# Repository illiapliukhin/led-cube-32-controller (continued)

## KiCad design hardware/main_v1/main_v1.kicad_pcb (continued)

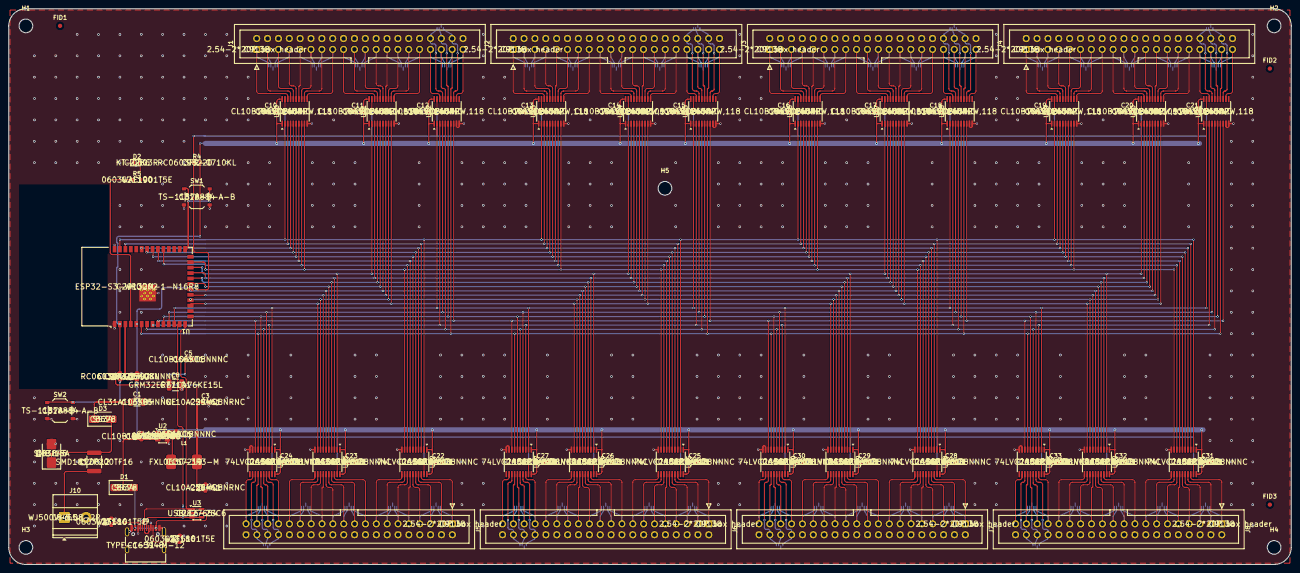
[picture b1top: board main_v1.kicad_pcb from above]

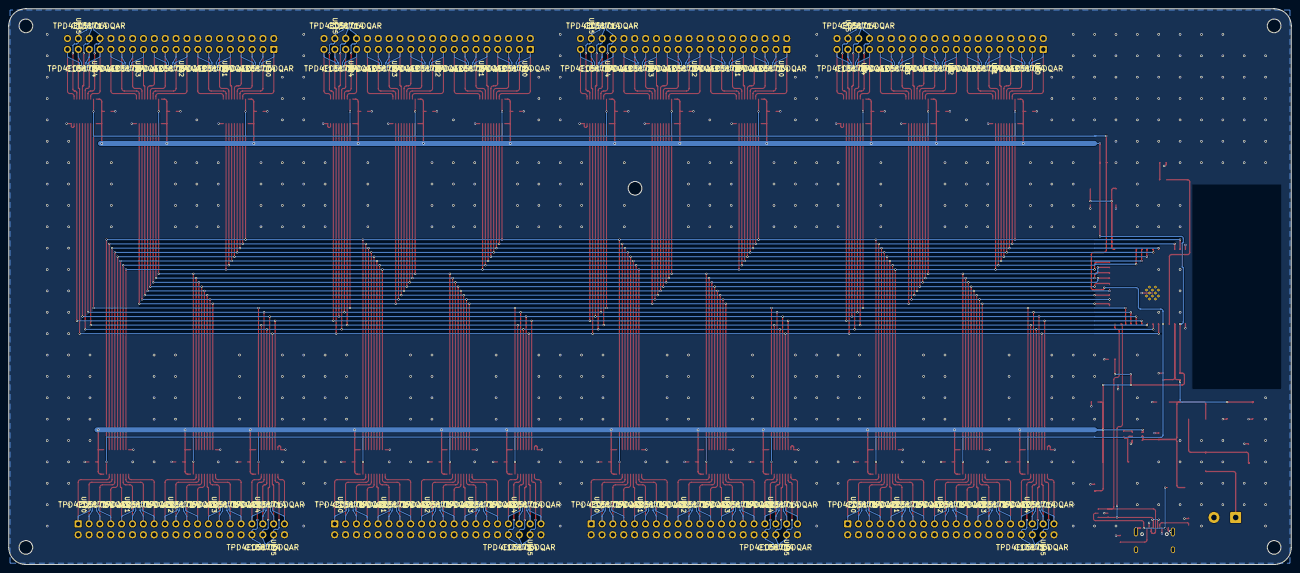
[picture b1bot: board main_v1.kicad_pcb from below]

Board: 2 copper layers, 300.0 x 130.0 mm, 138 parts (48 on the bottom side), 224 nets.

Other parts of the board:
FID1, FID2, FID3: FID; Fiducial_1mm_Mask2mm
H1, H2, H3, H4, H5: M3; MountingHole_3.2mm_M3

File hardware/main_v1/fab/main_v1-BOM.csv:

Comment,Designator,Footprint,LCSC Part #,MPN,Qty
10uF50V,C1,C_1206_3216Metric,C13585,CL31A106KBHNNNE,1
100nF,"C10,C11,C12,C13,C14,C15,C16,C17,C18,C19,C2,C20,C21,C22,C23,C24,C25,C26,C27,C28,C29,C30,C31,C32,C33,C5,C7",C_0603_1608Metric,C66501,CL10B104KO8NNNC,27
22uF,"C3,C4",C_0603_1608Metric,C59461,CL10A226MQ8NRNC,2
1uF,C6,C_0603_1608Metric,C1592,CL10A105KO8NNNC,1
47uF,C8,C_1210_3225Metric,C77101,GRM32ER61C476KE15L,1
SS34,D1,D_SMA,C8678,SS34,1
STATUS,D2,LED_0603_1608Metric,C2286,KT-0603R,1
SS34 (rev.pol.),D3,D_SMA,C8678,SS34,1
SMBJ15A,D4,D_SMB,C83846,SMBJ15A,1
PTC 2A/16V,F1,Fuse_1812_4532Metric,C20812,SMD1812P200TF16,1
PORT0,J1,IDC-Header_2x20_P2.54mm_Vertical,C9138,2.54-2*20P box header,1
12V_IN,J10,"TerminalBlock_Phoenix_MKDS-1,5-2-5.08_1x02_P5.08mm_Horizontal",C8465,WJ500V-5.08-2P,1
PORT1,J2,IDC-Header_2x20_P2.54mm_Vertical,C9138,2.54-2*20P box header,1
PORT2,J3,IDC-Header_2x20_P2.54mm_Vertical,C9138,2.54-2*20P box header,1
PORT3,J4,IDC-Header_2x20_P2.54mm_Vertical,C9138,2.54-2*20P box header,1
PORT4,J5,IDC-Header_2x20_P2.54mm_Vertical,C9138,2.54-2*20P box header,1
PORT5,J6,IDC-Header_2x20_P2.54mm_Vertical,C9138,2.54-2*20P box header,1
PORT6,J7,IDC-Header_2x20_P2.54mm_Vertical,C9138,2.54-2*20P box header,1
PORT7,J8,IDC-Header_2x20_P2.54mm_Vertical,C9138,2.54-2*20P box header,1
USB-C,J9,USB_C_Receptacle_HRO_TYPE-C-31-M-12,C165948,TYPE-C-31-M-12,1
3.3uH,L1,L_Cjiang_FXL0630,C167219,FXL0630-3R3-M,1
10k,"R1,R4",R_0603_1608Metric,C98220,RC0603FR-0710KL,2
5.1k,"R2,R3",R_0603_1608Metric,C23186,0603WAF5101T5E,2
1k,R5,R_0603_1608Metric,C21190,0603WAF1001T5E,1
BOOT,SW1,SW_Push_1P1T_XKB_TS-1187A,C318884,TS-1187A-B-A-B,1
RESET,SW2,SW_Push_1P1T_XKB_TS-1187A,C318884,TS-1187A-B-A-B,1
ESP32-S3-WROOM-1-N16R8,U1,ESP32-S3-WROOM-1,C2913202,ESP32-S3-WROOM-1-N16R8,1
74LVC245APW,"U10,U11,U12,U13,U14,U15,U16,U17,U18,U19,U20,U21,U22,U23,U24,U25,U26,U27,U28,U29,U30,U31,U32,U33",TSSOP-20_4.4x6.5mm_P0.65mm,C6082,"74LVC245APW,118",24
AP63203WU-7,U2,TSOT-23-6,C780769,AP63203WU-7,1
USBLC6-2SC6,U3,SOT-23-6,C2827654,USBLC6-2SC6,1
TPD4E05U06DQAR,"UE0,UE1,UE10,UE11,UE12,UE13,UE14,UE15,UE2,UE20,UE21,UE22,UE23,UE24,UE25,UE3,UE30,UE31,UE32,UE33,UE34,UE35,UE4,UE40,UE41,UE42,UE43,UE44,UE45,UE5,UE50,UE51,UE52,UE53,UE54,UE55,UE60,UE61,UE62,UE63,UE64,UE65,UE70,UE71,UE72,UE73,UE74,UE75",USON-10_2.5x1.0mm_P0.5mm,C138714,TPD4E05U06DQAR,48

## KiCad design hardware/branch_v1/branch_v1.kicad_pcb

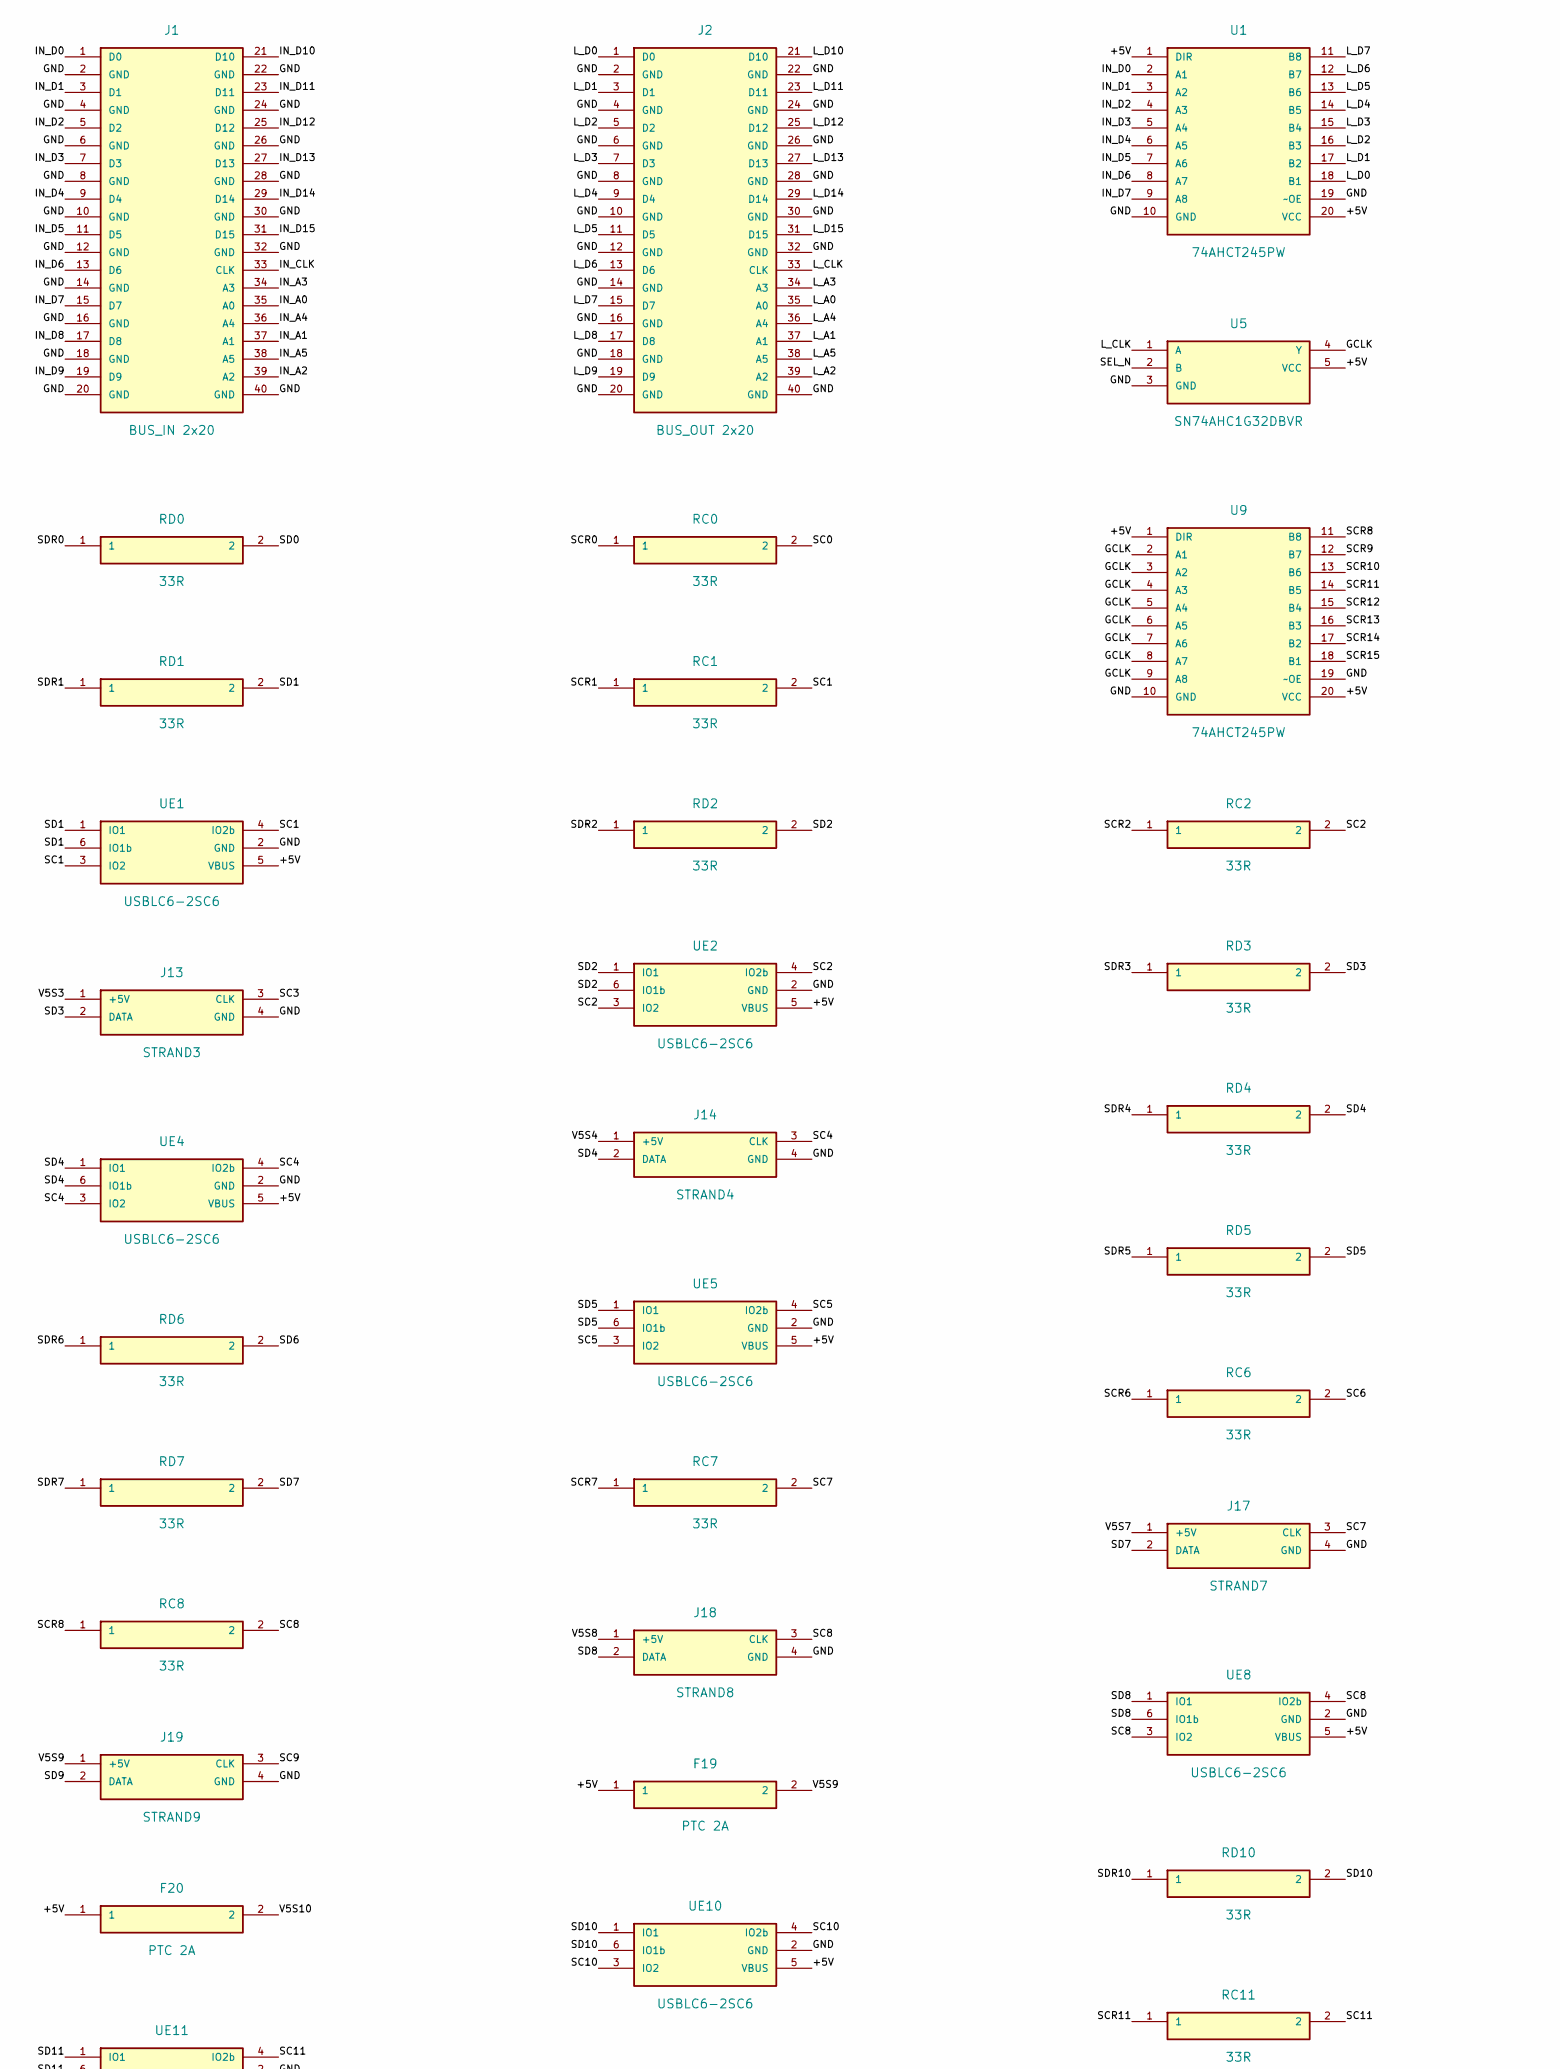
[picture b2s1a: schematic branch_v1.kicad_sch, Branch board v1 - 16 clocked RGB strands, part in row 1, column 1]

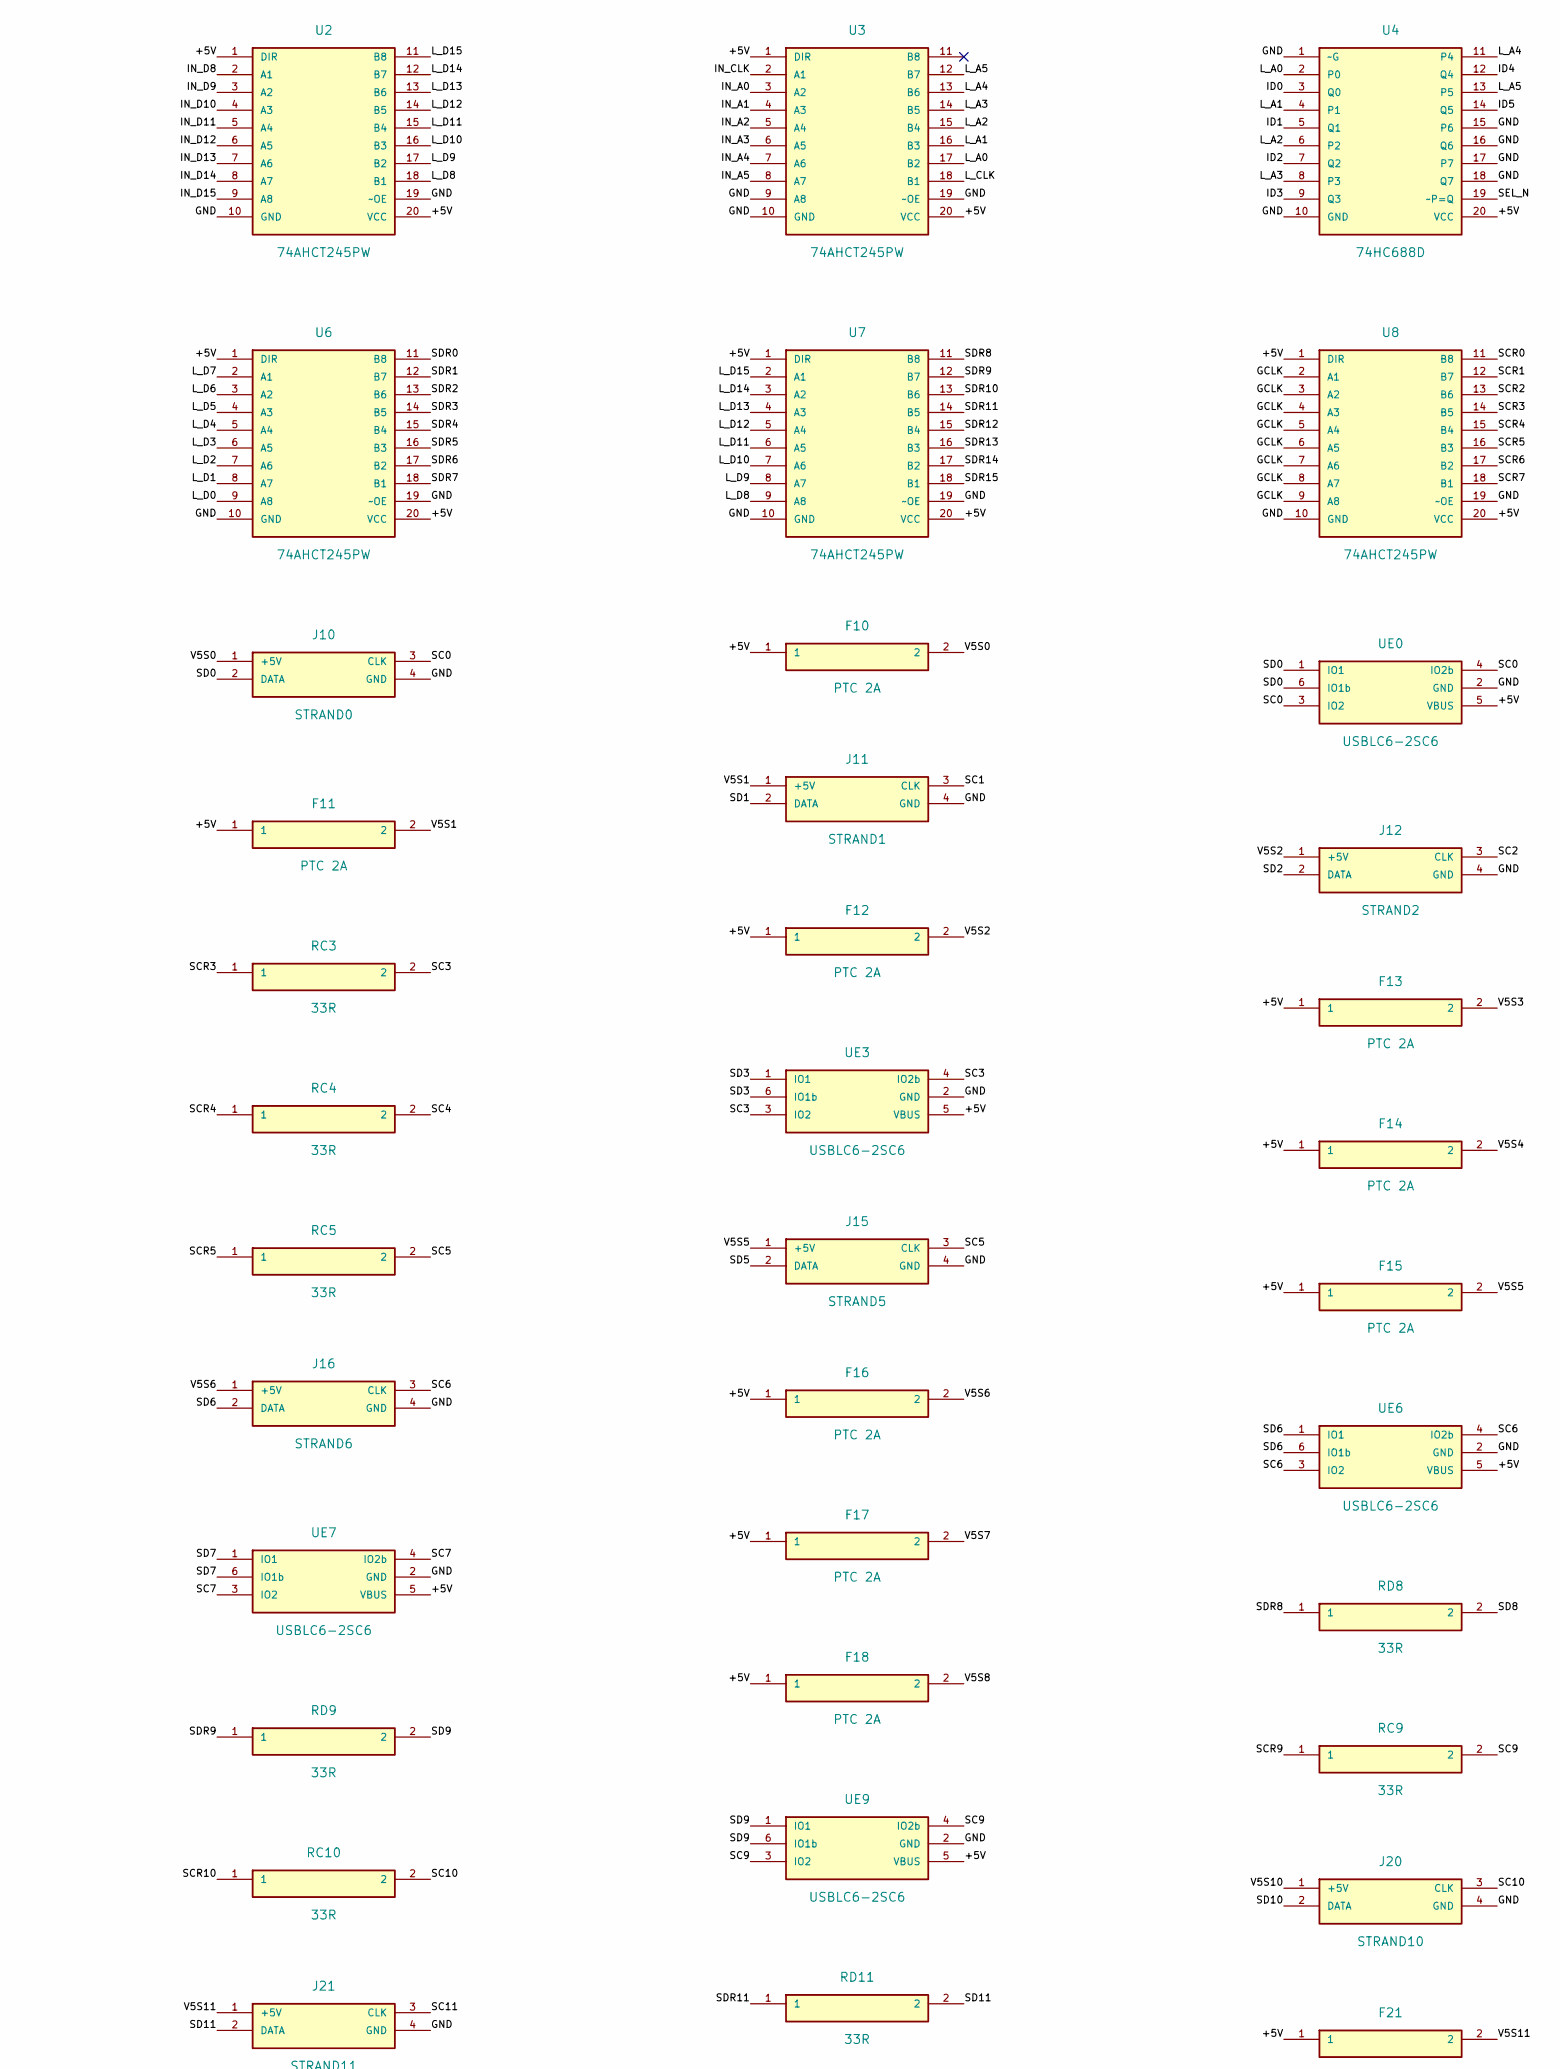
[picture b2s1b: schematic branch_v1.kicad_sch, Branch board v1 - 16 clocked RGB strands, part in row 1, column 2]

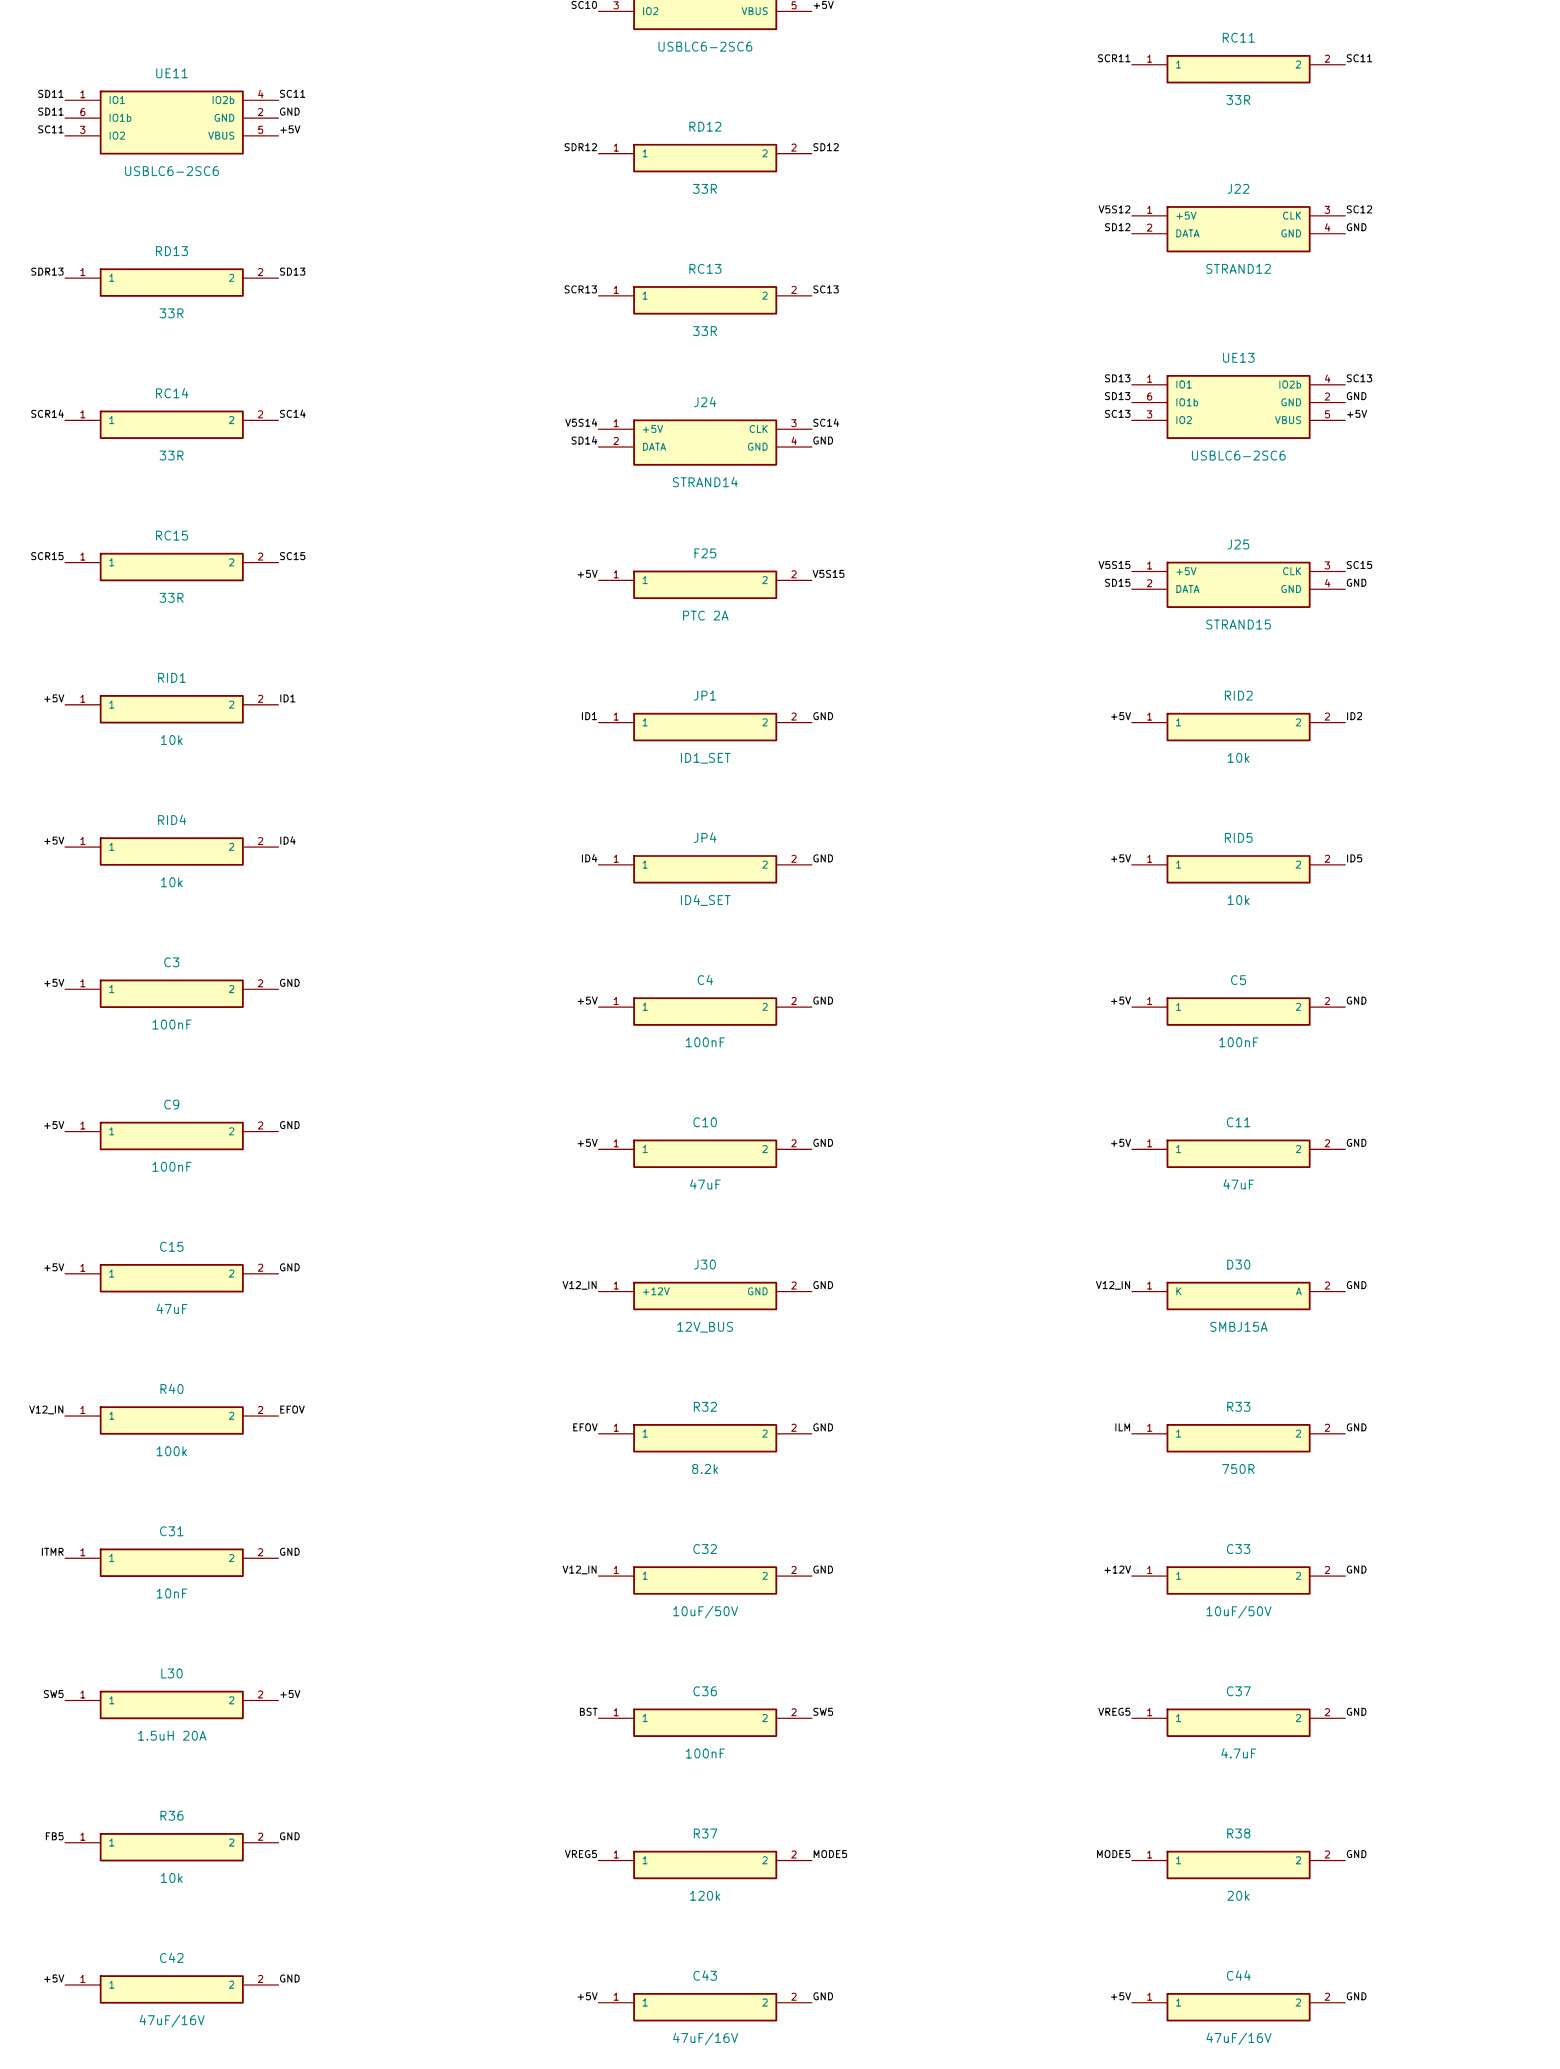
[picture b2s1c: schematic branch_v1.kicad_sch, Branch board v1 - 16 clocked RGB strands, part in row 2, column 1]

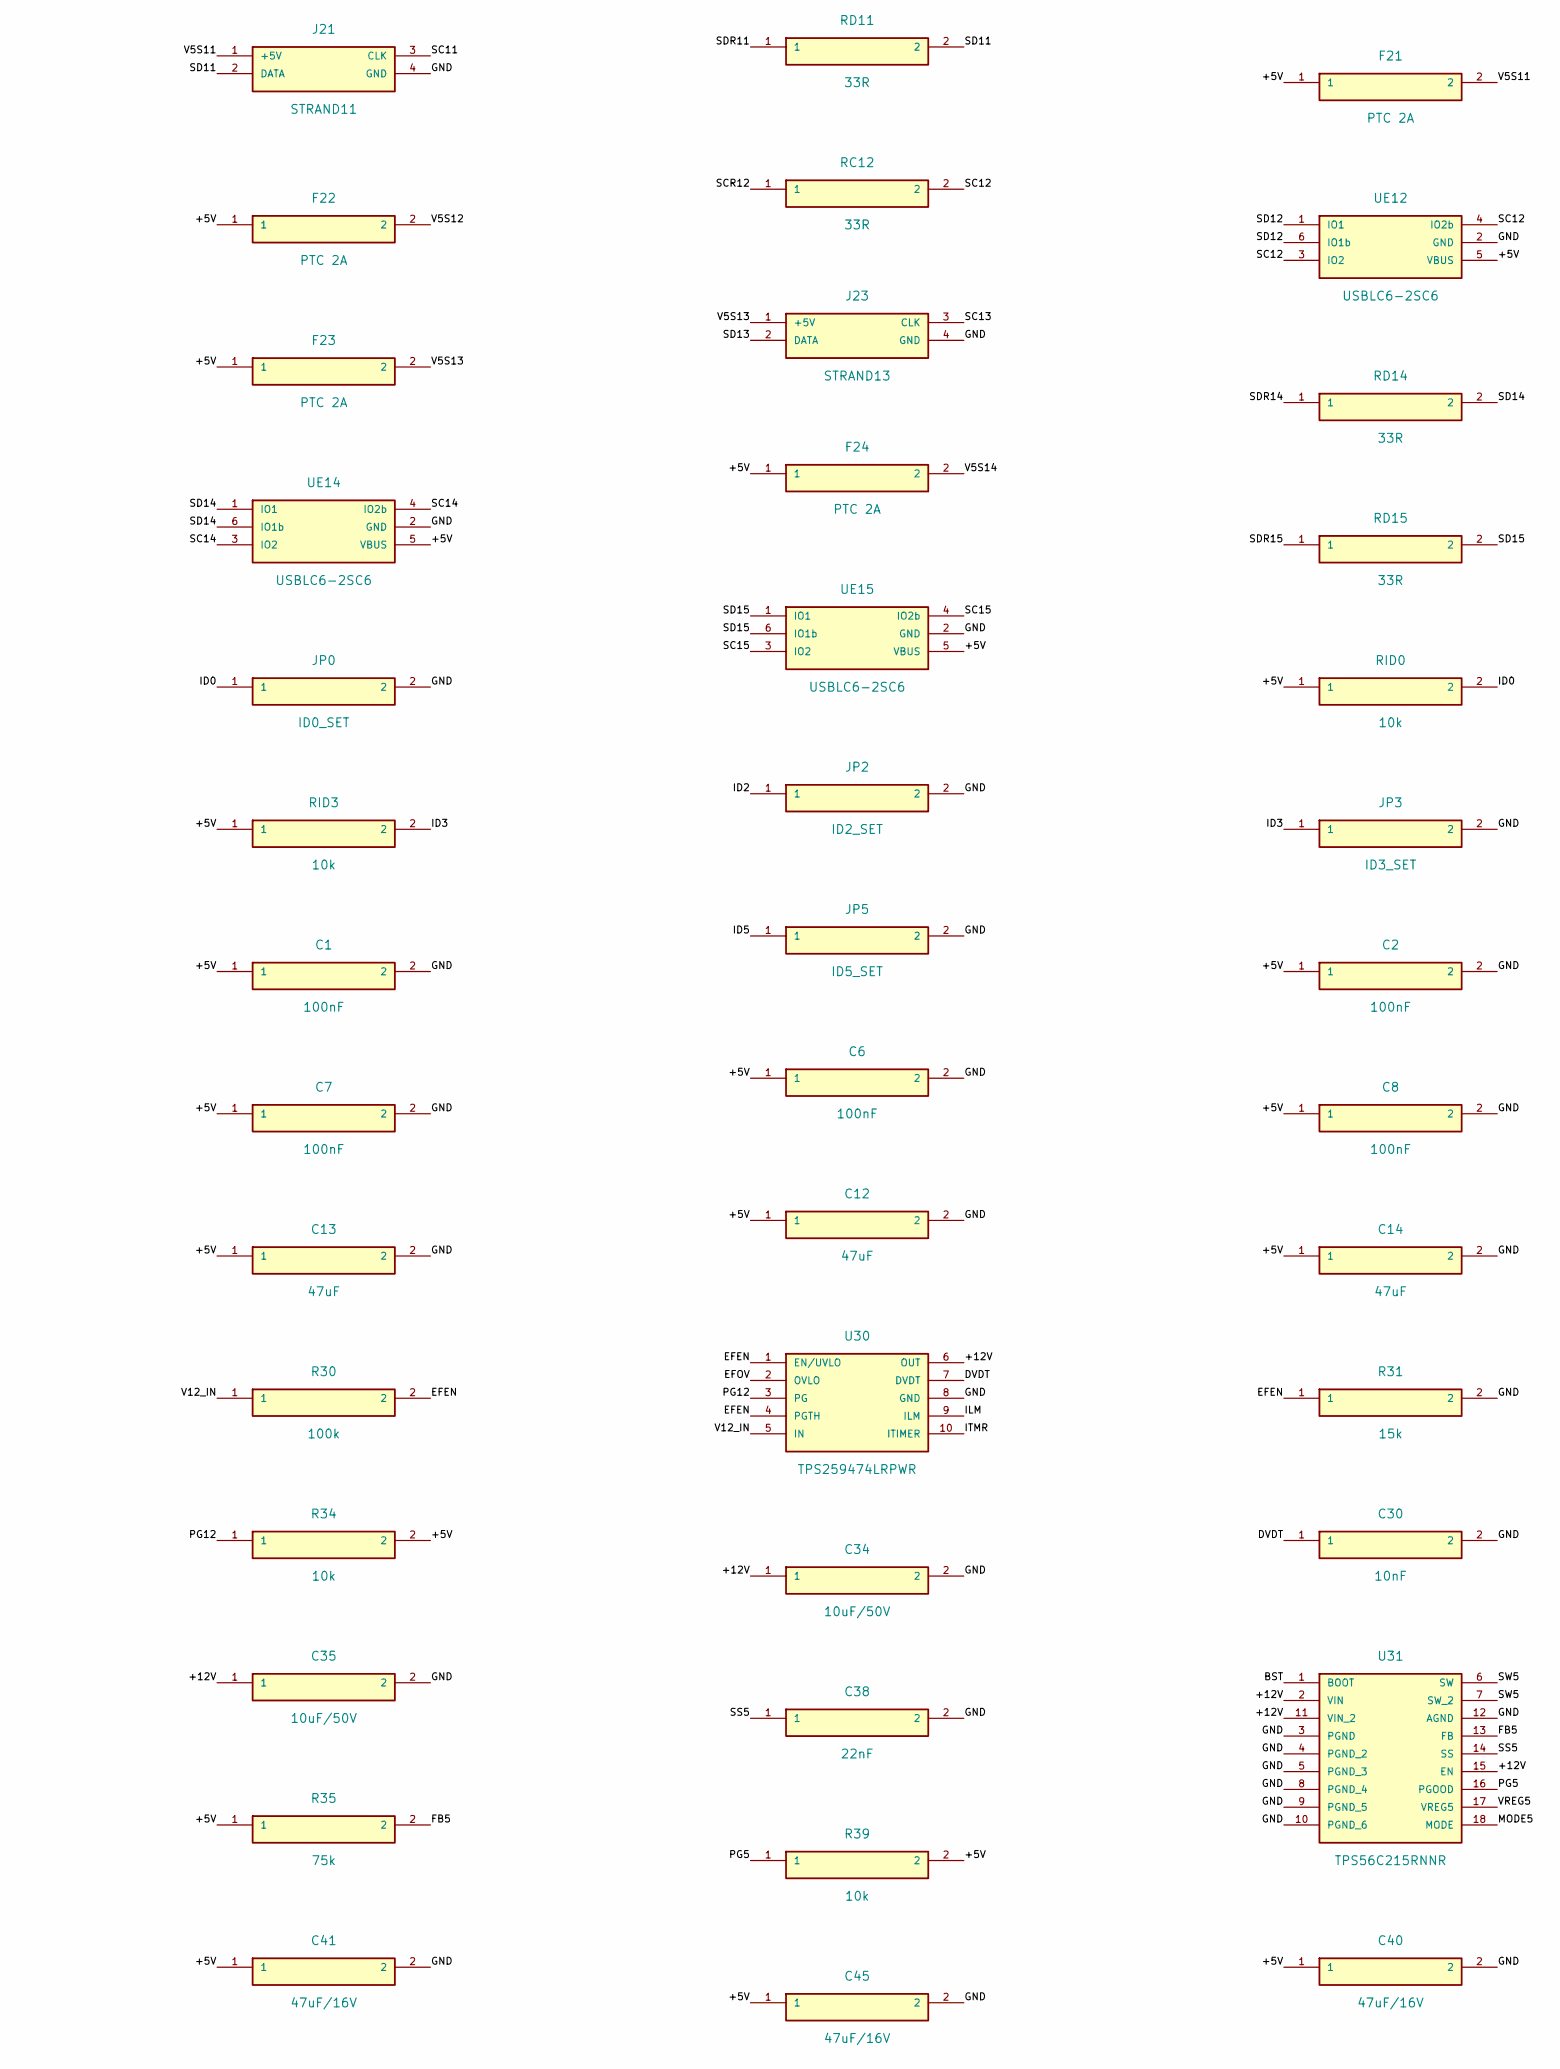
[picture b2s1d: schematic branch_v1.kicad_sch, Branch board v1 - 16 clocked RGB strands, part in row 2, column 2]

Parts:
C1, C2, C3, C4, C5, C6, C7, C8, C9, C36: 100nF; C_0603_1608Metric; MPN CL10B104KO8NNNC; LCSC C66501
C10, C11, C12, C13, C14, C15: 47uF; C_0805_2012Metric; MPN CL21A476MQYNNNE; LCSC C16780
C30, C31: 10nF; C_0603_1608Metric; MPN 0603B103K500NT; LCSC C57112
C32, C33, C34, C35: 10uF/50V; C_1206_3216Metric; MPN CL31A106KBHNNNE; LCSC C13585
C37: 4.7uF; C_0603_1608Metric; MPN CL10A475KO8NNNC; LCSC C19666
C38: 22nF; C_0603_1608Metric; MPN CL10B223KB8NNNC; LCSC C21122
C40, C41, C42, C43, C44, C45: 47uF/16V; C_1210_3225Metric; MPN GRM32ER61C476KE15L; LCSC C77101
D30: SMBJ15A; D_SMB; MPN SMBJ15A; LCSC C83846
F10, F11, F12, F13, F14, F15, F16, F17, F18, F19, F20, F21, F22, F23, F24, F25: PTC 2A; Fuse_1812_4532Metric; MPN SMD1812P200TF16; LCSC C20812
J1: BUS_IN 2x20; IDC-Header_2x20_P2.54mm_Vertical; MPN 2.54-2*20P; LCSC C9138
J2: BUS_OUT 2x20; IDC-Header_2x20_P2.54mm_Vertical; MPN 2.54-2*20P; LCSC C9138
J10: STRAND0; JST_XH_B4B-XH-A_1x04_P2.50mm_Vertical; MPN B4B-XH-A(LF)(SN); LCSC C144395
J11: STRAND1; JST_XH_B4B-XH-A_1x04_P2.50mm_Vertical; MPN B4B-XH-A(LF)(SN); LCSC C144395
J12: STRAND2; JST_XH_B4B-XH-A_1x04_P2.50mm_Vertical; MPN B4B-XH-A(LF)(SN); LCSC C144395
J13: STRAND3; JST_XH_B4B-XH-A_1x04_P2.50mm_Vertical; MPN B4B-XH-A(LF)(SN); LCSC C144395
J14: STRAND4; JST_XH_B4B-XH-A_1x04_P2.50mm_Vertical; MPN B4B-XH-A(LF)(SN); LCSC C144395
J15: STRAND5; JST_XH_B4B-XH-A_1x04_P2.50mm_Vertical; MPN B4B-XH-A(LF)(SN); LCSC C144395
J16: STRAND6; JST_XH_B4B-XH-A_1x04_P2.50mm_Vertical; MPN B4B-XH-A(LF)(SN); LCSC C144395
J17: STRAND7; JST_XH_B4B-XH-A_1x04_P2.50mm_Vertical; MPN B4B-XH-A(LF)(SN); LCSC C144395
J18: STRAND8; JST_XH_B4B-XH-A_1x04_P2.50mm_Vertical; MPN B4B-XH-A(LF)(SN); LCSC C144395
J19: STRAND9; JST_XH_B4B-XH-A_1x04_P2.50mm_Vertical; MPN B4B-XH-A(LF)(SN); LCSC C144395
J20: STRAND10; JST_XH_B4B-XH-A_1x04_P2.50mm_Vertical; MPN B4B-XH-A(LF)(SN); LCSC C144395
J21: STRAND11; JST_XH_B4B-XH-A_1x04_P2.50mm_Vertical; MPN B4B-XH-A(LF)(SN); LCSC C144395
J22: STRAND12; JST_XH_B4B-XH-A_1x04_P2.50mm_Vertical; MPN B4B-XH-A(LF)(SN); LCSC C144395
J23: STRAND13; JST_XH_B4B-XH-A_1x04_P2.50mm_Vertical; MPN B4B-XH-A(LF)(SN); LCSC C144395
J24: STRAND14; JST_XH_B4B-XH-A_1x04_P2.50mm_Vertical; MPN B4B-XH-A(LF)(SN); LCSC C144395
J25: STRAND15; JST_XH_B4B-XH-A_1x04_P2.50mm_Vertical; MPN B4B-XH-A(LF)(SN); LCSC C144395
J30: 12V_BUS; TerminalBlock_Phoenix_MKDS-1,5-2-5.08_1x02_P5.08mm_Horizont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; MPN WJ500V-5.08-2P; LCSC C8465
JP0: ID0_SET; SolderJumper-2_P1.3mm_Open_RoundedPad1.0x1.5mm
JP1: ID1_SET; SolderJumper-2_P1.3mm_Open_RoundedPad1.0x1.5mm
JP2: ID2_SET; SolderJumper-2_P1.3mm_Open_RoundedPad1.0x1.5mm
JP3: ID3_SET; SolderJumper-2_P1.3mm_Open_RoundedPad1.0x1.5mm
JP4: ID4_SET; SolderJumper-2_P1.3mm_Open_RoundedPad1.0x1.5mm
JP5: ID5_SET; SolderJumper-2_P1.3mm_Open_RoundedPad1.0x1.5mm
L30: 1.5uH 20A; L_YJYCOIN_YSPI1365; MPN YSPI1365-1R5M; LCSC C5158939
R30, R40: 100k; R_0603_1608Metric; MPN 0603WAF1003T5E; LCSC C25803
R31: 15k; R_0603_1608Metric; MPN 0603WAF1502T5E; LCSC C22809
R32: 8.2k; R_0603_1608Metric; MPN 0603WAF8201T5E; LCSC C25981
R33: 750R; R_0603_1608Metric; MPN 0603WAF7500T5E; LCSC C23241
R34, R36, R39: 10k; R_0603_1608Metric; MPN RC0603FR-0710KL; LCSC C98220
R35: 75k; R_0603_1608Metric; MPN 0603WAF7502T5E; LCSC C23242
R37: 120k; R_0603_1608Metric; MPN 0603WAF1203T5E; LCSC C25808
R38: 20k; R_0603_1608Metric; MPN 0603WAF2002T5E; LCSC C4184
RC0, RC1, RC2, RC3, RC4, RC5, RC6, RC7, RC8, RC9, RC10, RC11, RC12, RC13, RC14, RC15: 33R; R_0603_1608Metric; MPN 0603WAF330JT5E; LCSC C23140
RD0, RD1, RD2, RD3, RD4, RD5, RD6, RD7, RD8, RD9, RD10, RD11, RD12, RD13, RD14, RD15: 33R; R_0603_1608Metric; MPN 0603WAF330JT5E; LCSC C23140
RID0, RID1, RID2, RID3, RID4, RID5: 10k; R_0603_1608Metric; MPN RC0603FR-0710KL; LCSC C98220
U1, U2, U3, U6, U7, U8, U9: 74AHCT245PW; TSSOP-20_4.4x6.5mm_P0.65mm; MPN 74AHCT245PW,118; LCSC C173388
U4: 74HC688D; SOIC-20W_7.5x12.8mm_P1.27mm; MPN 74HC688D,653; LCSC C88042
U5: SN74AHC1G32DBVR; SOT-23-5; MPN SN74AHC1G32DBVR; LCSC C7470
U30: TPS259474LRPWR; TI_RPW0010A_VQFN-HR-10_2x2mm_P0.45mm; MPN TPS259474LRPWR; LCSC C2864845
U31: TPS56C215RNNR; Texas_RNN0018A; MPN TPS56C215RNNR; LCSC C473372
UE0, UE1, UE2, UE3, UE4, UE5, UE6, UE7, UE8, UE9, UE10, UE11, UE12, UE13, UE14, UE15: USBLC6-2SC6; SOT-23-6; MPN USBLC6-2SC6; LCSC C2827654

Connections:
/+5V: C1.1, C2.1, C3.1, C4.1, C5.1, C6.1, C7.1, C8.1, C9.1, C10.1, C11.1, C12.1, C13.1, C14.1, C15.1, C40.1, C41.1, C42.1, C43.1, C44.1, C45.1, F10.1, F11.1, F12.1, F13.1, F14.1, F15.1, F16.1, F17.1, F18.1, F19.1, F20.1, F21.1, F22.1, F23.1, F24.1, F25.1, L30.2, R34.2, R35.1, R39.2, RID0.1, RID1.1, RID2.1, RID3.1, RID4.1, RID5.1, U1.1 (DIR), U1.20 (VCC), U2.1 (DIR), U2.20 (VCC), U3.1 (DIR), U3.20 (VCC), U4.20 (VCC), U5.5 (VCC), U6.1 (DIR), U6.20 (VCC), U7.1 (DIR), U7.20 (VCC), U8.1 (DIR), U8.20 (VCC), U9.1 (DIR), U9.20 (VCC), UE0.5 (VBUS), UE1.5 (VBUS), UE2.5 (VBUS), UE3.5 (VBUS), UE4.5 (VBUS), UE5.5 (VBUS), UE6.5 (VBUS), UE7.5 (VBUS), UE8.5 (VBUS), UE9.5 (VBUS), UE10.5 (VBUS), UE11.5 (VBUS), UE12.5 (VBUS), UE13.5 (VBUS), UE14.5 (VBUS), UE15.5 (VBUS)
/+12V: C33.1, C34.1, C35.1, U30.6 (OUT), U31.2 (VIN), U31.11 (VIN_2), U31.15 (EN)
/BST: C36.1, U31.1 (BOOT)
/DVDT: C30.1, U30.7 (DVDT)
/EFEN: R30.2, R31.1, U30.1 (EN/UVLO), U30.4 (PGTH)
/EFOV: R32.1, R40.2, U30.2 (OVLO)
/FB5: R35.2, R36.1, U31.13 (FB)
/GCLK: U5.4 (Y), U8.2 (A1), U8.3 (A2), U8.4 (A3), U8.5 (A4), U8.6 (A5), U8.7 (A6), U8.8 (A7), U8.9 (A8), U9.2 (A1), U9.3 (A2), U9.4 (A3), U9.5 (A4), U9.6 (A5), U9.7 (A6), U9.8 (A7), U9.9 (A8)
/GND: C1.2, C2.2, C3.2, C4.2, C5.2, C6.2, C7.2, C8.2, C9.2, C10.2, C11.2, C12.2, C13.2, C14.2, C15.2, C30.2, C31.2, C32.2, C33.2, C34.2, C35.2, C37.2, C38.2, C40.2, C41.2, C42.2, C43.2, C44.2, C45.2, D30.2 (A), J1.2 (GND), J1.4 (GND), J1.6 (GND), J1.8 (GND), J1.10 (GND), J1.12 (GND), J1.14 (GND), J1.16 (GND), J1.18 (GND), J1.20 (GND), J1.22 (GND), J1.24 (GND), J1.26 (GND), J1.28 (GND), J1.30 (GND), J1.32 (GND), J1.40 (GND), J2.2 (GND), J2.4 (GND), J2.6 (GND), J2.8 (GND), J2.10 (GND), J2.12 (GND), J2.14 (GND), J2.16 (GND), J2.18 (GND), J2.20 (GND), J2.22 (GND), J2.24 (GND), J2.26 (GND), J2.28 (GND), J2.30 (GND), J2.32 (GND), J2.40 (GND), J10.4 (GND), J11.4 (GND), J12.4 (GND), J13.4 (GND), J14.4 (GND), J15.4 (GND), J16.4 (GND), J17.4 (GND), J18.4 (GND), J19.4 (GND), J20.4 (GND), J21.4 (GND), J22.4 (GND), J23.4 (GND), J24.4 (GND), J25.4 (GND), J30.2 (GND), JP0.2, JP1.2, JP2.2, JP3.2, JP4.2, JP5.2, R31.2, R32.2, R33.2, R36.2, R38.2, U1.10 (GND), U1.19 (~OE), U2.10 (GND), U2.19 (~OE), U3.9 (A8), U3.10 (GND), U3.19 (~OE), U4.1 (~G), U4.10 (GND), U4.15 (P6), U4.16 (Q6), U4.17 (P7), U4.18 (Q7), U5.3 (GND), U6.10 (GND), U6.19 (~OE), U7.10 (GND), U7.19 (~OE), U8.10 (GND), U8.19 (~OE), U9.10 (GND), U9.19 (~OE), U30.8 (GND), U31.3 (PGND), U31.4 (PGND_2), U31.5 (PGND_3), U31.8 (PGND_4), U31.9 (PGND_5), U31.10 (PGND_6), U31.12 (AGND), UE0.2 (GND), UE1.2 (GND), UE2.2 (GND), UE3.2 (GND), UE4.2 (GND), UE5.2 (GND), UE6.2 (GND), UE7.2 (GND), UE8.2 (GND), UE9.2 (GND), UE10.2 (GND), UE11.2 (GND), UE12.2 (GND), UE13.2 (GND), UE14.2 (GND), UE15.2 (GND)
/ID0: JP0.1, RID0.2, U4.3 (Q0)
/ID1: JP1.1, RID1.2, U4.5 (Q1)
/ID2: JP2.1, RID2.2, U4.7 (Q2)
/ID3: JP3.1, RID3.2, U4.9 (Q3)
/ID4: JP4.1, RID4.2, U4.12 (Q4)
/ID5: JP5.1, RID5.2, U4.14 (Q5)
/ILM: R33.1, U30.9 (ILM)
/IN_A0: J1.35 (A0), U3.3 (A2)
/IN_A1: J1.37 (A1), U3.4 (A3)
/IN_A2: J1.39 (A2), U3.5 (A4)
/IN_A3: J1.34 (A3), U3.6 (A5)
/IN_A4: J1.36 (A4), U3.7 (A6)
/IN_A5: J1.38 (A5), U3.8 (A7)
/IN_CLK: J1.33 (CLK), U3.2 (A1)
/IN_D0: J1.1 (D0), U1.2 (A1)
/IN_D1: J1.3 (D1), U1.3 (A2)
/IN_D2: J1.5 (D2), U1.4 (A3)
/IN_D3: J1.7 (D3), U1.5 (A4)
/IN_D4: J1.9 (D4), U1.6 (A5)
/IN_D5: J1.11 (D5), U1.7 (A6)
/IN_D6: J1.13 (D6), U1.8 (A7)
/IN_D7: J1.15 (D7), U1.9 (A8)
/IN_D8: J1.17 (D8), U2.2 (A1)
/IN_D9: J1.19 (D9), U2.3 (A2)
/IN_D10: J1.21 (D10), U2.4 (A3)
/IN_D11: J1.23 (D11), U2.5 (A4)
/IN_D12: J1.25 (D12), U2.6 (A5)
/IN_D13: J1.27 (D13), U2.7 (A6)
/IN_D14: J1.29 (D14), U2.8 (A7)
/IN_D15: J1.31 (D15), U2.9 (A8)
/ITMR: C31.1, U30.10 (ITIMER)
/L_A0: J2.35 (A0), U3.17 (B2), U4.2 (P0)
/L_A1: J2.37 (A1), U3.16 (B3), U4.4 (P1)
/L_A2: J2.39 (A2), U3.15 (B4), U4.6 (P2)
/L_A3: J2.34 (A3), U3.14 (B5), U4.8 (P3)
/L_A4: J2.36 (A4), U3.13 (B6), U4.11 (P4)
/L_A5: J2.38 (A5), U3.12 (B7), U4.13 (P5)
/L_CLK: J2.33 (CLK), U3.18 (B1), U5.1 (A)
/L_D0: J2.1 (D0), U1.18 (B1), U6.9 (A8)
/L_D1: J2.3 (D1), U1.17 (B2), U6.8 (A7)
/L_D2: J2.5 (D2), U1.16 (B3), U6.7 (A6)
/L_D3: J2.7 (D3), U1.15 (B4), U6.6 (A5)
/L_D4: J2.9 (D4), U1.14 (B5), U6.5 (A4)
/L_D5: J2.11 (D5), U1.13 (B6), U6.4 (A3)
/L_D6: J2.13 (D6), U1.12 (B7), U6.3 (A2)
/L_D7: J2.15 (D7), U1.11 (B8), U6.2 (A1)
/L_D8: J2.17 (D8), U2.18 (B1), U7.9 (A8)
/L_D9: J2.19 (D9), U2.17 (B2), U7.8 (A7)
/L_D10: J2.21 (D10), U2.16 (B3), U7.7 (A6)
/L_D11: J2.23 (D11), U2.15 (B4), U7.6 (A5)
/L_D12: J2.25 (D12), U2.14 (B5), U7.5 (A4)
/L_D13: J2.27 (D13), U2.13 (B6), U7.4 (A3)
/L_D14: J2.29 (D14), U2.12 (B7), U7.3 (A2)
/L_D15: J2.31 (D15), U2.11 (B8), U7.2 (A1)
/MODE5: R37.2, R38.1, U31.18 (MODE)
/PG5: R39.1, U31.16 (PGOOD)
/PG12: R34.1, U30.3 (PG)
/SC0: J10.3 (CLK), RC0.2, UE0.3 (IO2), UE0.4 (IO2b)
/SC1: J11.3 (CLK), RC1.2, UE1.3 (IO2), UE1.4 (IO2b)
/SC2: J12.3 (CLK), RC2.2, UE2.3 (IO2), UE2.4 (IO2b)
/SC3: J13.3 (CLK), RC3.2, UE3.3 (IO2), UE3.4 (IO2b)
/SC4: J14.3 (CLK), RC4.2, UE4.3 (IO2), UE4.4 (IO2b)
/SC5: J15.3 (CLK), RC5.2, UE5.3 (IO2), UE5.4 (IO2b)
/SC6: J16.3 (CLK), RC6.2, UE6.3 (IO2), UE6.4 (IO2b)
/SC7: J17.3 (CLK), RC7.2, UE7.3 (IO2), UE7.4 (IO2b)
/SC8: J18.3 (CLK), RC8.2, UE8.3 (IO2), UE8.4 (IO2b)
/SC9: J19.3 (CLK), RC9.2, UE9.3 (IO2), UE9.4 (IO2b)
/SC10: J20.3 (CLK), RC10.2, UE10.3 (IO2), UE10.4 (IO2b)
/SC11: J21.3 (CLK), RC11.2, UE11.3 (IO2), UE11.4 (IO2b)
/SC12: J22.3 (CLK), RC12.2, UE12.3 (IO2), UE12.4 (IO2b)
/SC13: J23.3 (CLK), RC13.2, UE13.3 (IO2), UE13.4 (IO2b)
/SC14: J24.3 (CLK), RC14.2, UE14.3 (IO2), UE14.4 (IO2b)
/SC15: J25.3 (CLK), RC15.2, UE15.3 (IO2), UE15.4 (IO2b)
/SCR0: RC0.1, U8.11 (B8)
/SCR1: RC1.1, U8.12 (B7)
/SCR2: RC2.1, U8.13 (B6)
/SCR3: RC3.1, U8.14 (B5)
/SCR4: RC4.1, U8.15 (B4)
/SCR5: RC5.1, U8.16 (B3)
/SCR6: RC6.1, U8.17 (B2)
/SCR7: RC7.1, U8.18 (B1)
/SCR8: RC8.1, U9.11 (B8)
/SCR9: RC9.1, U9.12 (B7)
/SCR10: RC10.1, U9.13 (B6)
/SCR11: RC11.1, U9.14 (B5)
/SCR12: RC12.1, U9.15 (B4)
/SCR13: RC13.1, U9.16 (B3)
/SCR14: RC14.1, U9.17 (B2)
/SCR15: RC15.1, U9.18 (B1)
/SD0: J10.2 (DATA), RD0.2, UE0.1 (IO1), UE0.6 (IO1b)
/SD1: J11.2 (DATA), RD1.2, UE1.1 (IO1), UE1.6 (IO1b)
/SD2: J12.2 (DATA), RD2.2, UE2.1 (IO1), UE2.6 (IO1b)
/SD3: J13.2 (DATA), RD3.2, UE3.1 (IO1), UE3.6 (IO1b)
/SD4: J14.2 (DATA), RD4.2, UE4.1 (IO1), UE4.6 (IO1b)
/SD5: J15.2 (DATA), RD5.2, UE5.1 (IO1), UE5.6 (IO1b)
/SD6: J16.2 (DATA), RD6.2, UE6.1 (IO1), UE6.6 (IO1b)
/SD7: J17.2 (DATA), RD7.2, UE7.1 (IO1), UE7.6 (IO1b)
/SD8: J18.2 (DATA), RD8.2, UE8.1 (IO1), UE8.6 (IO1b)
/SD9: J19.2 (DATA), RD9.2, UE9.1 (IO1), UE9.6 (IO1b)
/SD10: J20.2 (DATA), RD10.2, UE10.1 (IO1), UE10.6 (IO1b)
/SD11: J21.2 (DATA), RD11.2, UE11.1 (IO1), UE11.6 (IO1b)
/SD12: J22.2 (DATA), RD12.2, UE12.1 (IO1), UE12.6 (IO1b)
/SD13: J23.2 (DATA), RD13.2, UE13.1 (IO1), UE13.6 (IO1b)
/SD14: J24.2 (DATA), RD14.2, UE14.1 (IO1), UE14.6 (IO1b)
/SD15: J25.2 (DATA), RD15.2, UE15.1 (IO1), UE15.6 (IO1b)
/SDR0: RD0.1, U6.11 (B8)
/SDR1: RD1.1, U6.12 (B7)
/SDR2: RD2.1, U6.13 (B6)
/SDR3: RD3.1, U6.14 (B5)
/SDR4: RD4.1, U6.15 (B4)
/SDR5: RD5.1, U6.16 (B3)
/SDR6: RD6.1, U6.17 (B2)
/SDR7: RD7.1, U6.18 (B1)
/SDR8: RD8.1, U7.11 (B8)
/SDR9: RD9.1, U7.12 (B7)
/SDR10: RD10.1, U7.13 (B6)
/SDR11: RD11.1, U7.14 (B5)
/SDR12: RD12.1, U7.15 (B4)
/SDR13: RD13.1, U7.16 (B3)
/SDR14: RD14.1, U7.17 (B2)
/SDR15: RD15.1, U7.18 (B1)
/SEL_N: U4.19 (~P=Q), U5.2 (B)
/SS5: C38.1, U31.14 (SS)
/SW5: C36.2, L30.1, U31.6 (SW), U31.7 (SW_2)
/V5S0: F10.2, J10.1 (+5V)
/V5S1: F11.2, J11.1 (+5V)
/V5S2: F12.2, J12.1 (+5V)
/V5S3: F13.2, J13.1 (+5V)
/V5S4: F14.2, J14.1 (+5V)
/V5S5: F15.2, J15.1 (+5V)
/V5S6: F16.2, J16.1 (+5V)
/V5S7: F17.2, J17.1 (+5V)
/V5S8: F18.2, J18.1 (+5V)
/V5S9: F19.2, J19.1 (+5V)
/V5S10: F20.2, J20.1 (+5V)
/V5S11: F21.2, J21.1 (+5V)
/V5S12: F22.2, J22.1 (+5V)
/V5S13: F23.2, J23.1 (+5V)
/V5S14: F24.2, J24.1 (+5V)
/V5S15: F25.2, J25.1 (+5V)
/V12_IN: C32.1, D30.1 (K), J30.1 (+12V), R30.1, R40.1, U30.5 (IN)
/VREG5: C37.1, R37.1, U31.17 (VREG5)
